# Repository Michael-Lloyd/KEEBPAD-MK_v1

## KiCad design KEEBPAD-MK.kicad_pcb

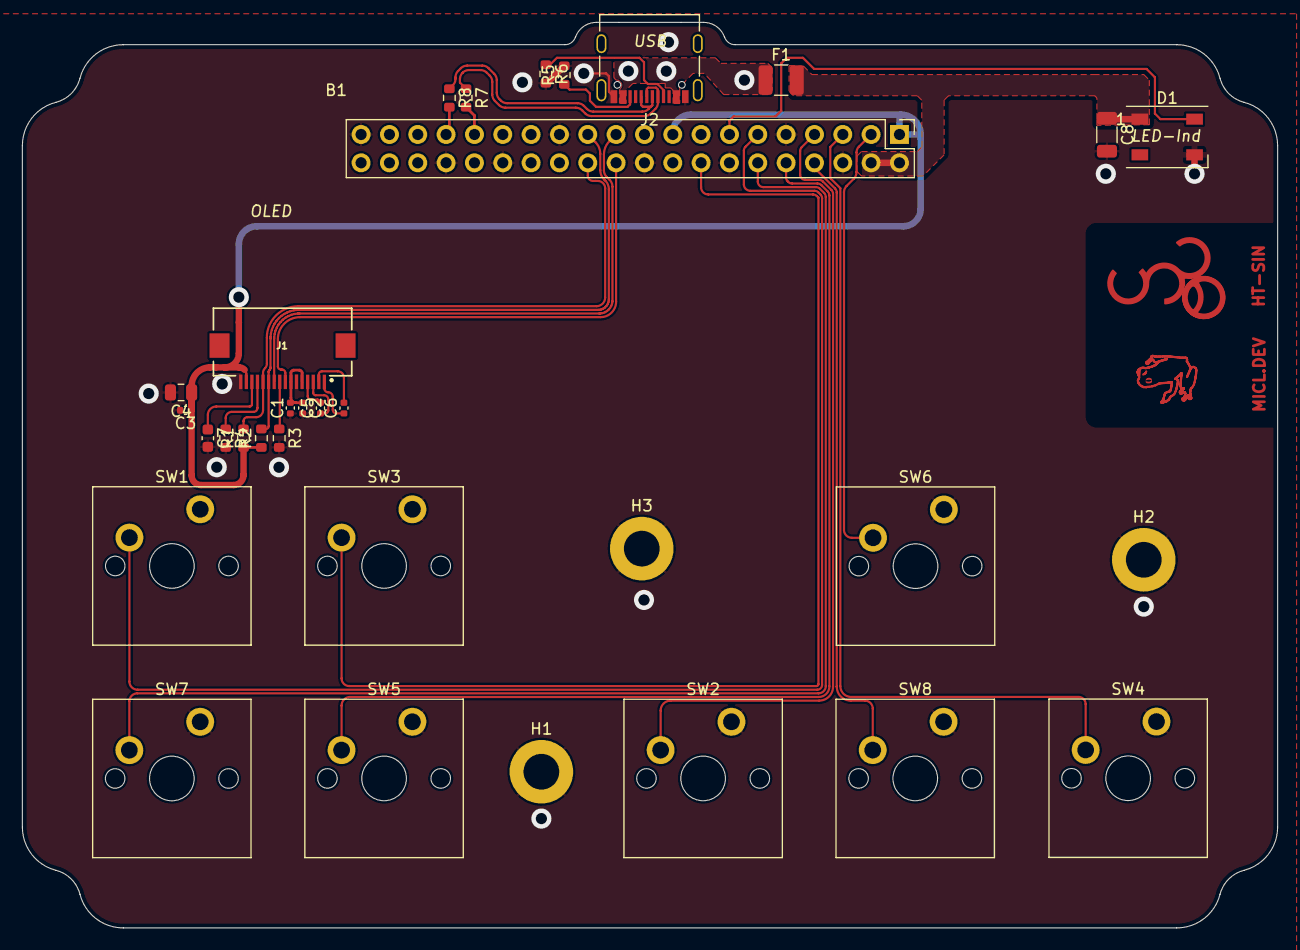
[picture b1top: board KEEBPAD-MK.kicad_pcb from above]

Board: 4 copper layers, 112.5 x 81.2 mm, 32 parts (0 on the bottom side), 31 nets.

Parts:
B1: GamePad
C1, C2: Not Specified; C_0402_1005Metric
C3, C5, C6: 1μF; C_0402_1005Metric
C4: 4.7μF; C_0805_2012Metric
C7: 2.2μF; C_0603_1608Metric
C8: 1μF; C_1206_3216Metric
D1: WS2812B; LED_WS2812B_PLCC4_5.0x5.0mm_P3.2mm
F1: Polyfuse; Fuse_1210_3225Metric
H1, H2, H3: MountingHole_Pad; MountingHole_3.2mm_M3_ISO7380_Pad
J1: SH1106G; GCT_FFC2B35-16
J2: USB_C_Receptacle_USB2.0; USB_C_Receptacle_Palconn_UTC16-G
R1, R2, R3: R; R_0603_1608Metric
R4: See Notes; R_0603_1608Metric
R5, R6: 5.1k; R_0603_1608Metric
R7, R8: 22Ω; R_0603_1608Metric
SW1, SW2, SW3, SW4, SW5, SW6, SW7, SW8: SW_SPST; SW_Cherry_MX_PCB

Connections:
+3V3: B1.1 (3.3V), B1.17 (3.3V), C3.1, C4.1, J1.15 (OLED_VIN), R1.1, R2.1
/128x64 OLED Display/IREF: J1.13 (IREF), R4.1
/128x64 OLED Display/VBAT: C1.2, C2.1, J1.5 (REG_VIN), J1.7 (LOGIC_VIN)
/128x64 OLED Display/VCOM_{H}: C7.1, J1.14 (VCOM_{H})
/128x64 OLED Display/~RESET: J1.9 (~RESET), R3.1
/D+: J2.A6 (D+), J2.B6 (D+), R8.1
/D-: J2.A7 (D-), J2.B7 (D-), R7.1
/Pinheader Assignments/$.ADC_{0}: B1.13 (GPIO26), D1.4 (DIN)
/Pinheader Assignments/$.ADC_{1}: B1.11 (GPIO27), SW1.1 (A)
/Pinheader Assignments/$.ADC_{2}: B1.12 (GPIO28), SW7.1 (A)
/Pinheader Assignments/$.ADC_{3}: B1.10 (GPIO29), SW5.1 (A)
/Pinheader Assignments/$.B: B1.3 (GPIO1/BUTTON_B), SW6.1 (A)
/Pinheader Assignments/$.GPIO_{6}: B1.7 (GPIO6), SW2.1 (A)
/Pinheader Assignments/$.GPIO_{10}: B1.33 (GPIO10), R8.2
/Pinheader Assignments/$.GPIO_{13}: B1.31 (GPIO13), R7.2
/Pinheader Assignments/$.GPIO_{20}: B1.21 (GPIO20), J1.10 (D/~C)
/Pinheader Assignments/$.GPIO_{22}: B1.16 (GPIO22), SW3.1 (A)
/Pinheader Assignments/$.SELECT: B1.8 (GPIO3/BUTTON_SELECT), SW8.1 (A)
/Pinheader Assignments/$.SPI^{0}_{SCK}: B1.23 (GPIO18), J1.11 (SCLK), R2.2
/Pinheader Assignments/$.SPI^{0}_{TX}: B1.24 (GPIO19), J1.12 (SD_{IN}/SDA/MOSI), R1.2
/Pinheader Assignments/$.SPI^{0}_{~CS}: B1.22 (GPIO21), J1.8 (~CS)
/Pinheader Assignments/$.START: B1.5 (GPIO2/BUTTON_START), SW4.1 (A)
GND: B1.6 (GND), B1.9 (GND), B1.14 (GND), B1.20 (GND), B1.25 (GND), B1.30 (GND), B1.34 (GND), B1.39 (GND), C1.1, C2.2, C3.2, C4.2, C7.2, C8.2, D1.3 (VSS), H1.1, H2.1, H3.1, J1.6 (GND/VSS), J1.16 (GND/VSS), J2.A1 (GND), J2.A12 (GND), J2.B1 (GND), J2.B12 (GND), R3.2, R4.2, R5.2, R6.2, SW1.2 (B), SW2.2 (B), SW3.2 (B), SW4.2 (B), SW5.2 (B), SW6.2 (B), SW7.2 (B), SW8.2 (B)
unnamed: C5.1, J1.3 (C_{1}+)
unnamed: C5.2, J1.4 (C_{1}-)
unnamed: C6.1, J1.1 (C_{2}+)
unnamed: C6.2, J1.2 (C_{2}-)
unnamed: F1.1, J2.A4 (VBUS), J2.A9 (VBUS), J2.B4 (VBUS), J2.B9 (VBUS)
unnamed: J2.A5 (CC1), R6.1
unnamed: J2.B5 (CC2), R5.1
VBUS: B1.2 (VBUS), B1.4 (VBUS), C8.1, D1.1 (VDD), F1.2

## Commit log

2022-10-07 Missing gerbers
2022-10-08 Fixed submodule ref
2022-10-08 Fixed pin assignments
2022-10-08 Fixed SPI pin assignments to SPI0 only
